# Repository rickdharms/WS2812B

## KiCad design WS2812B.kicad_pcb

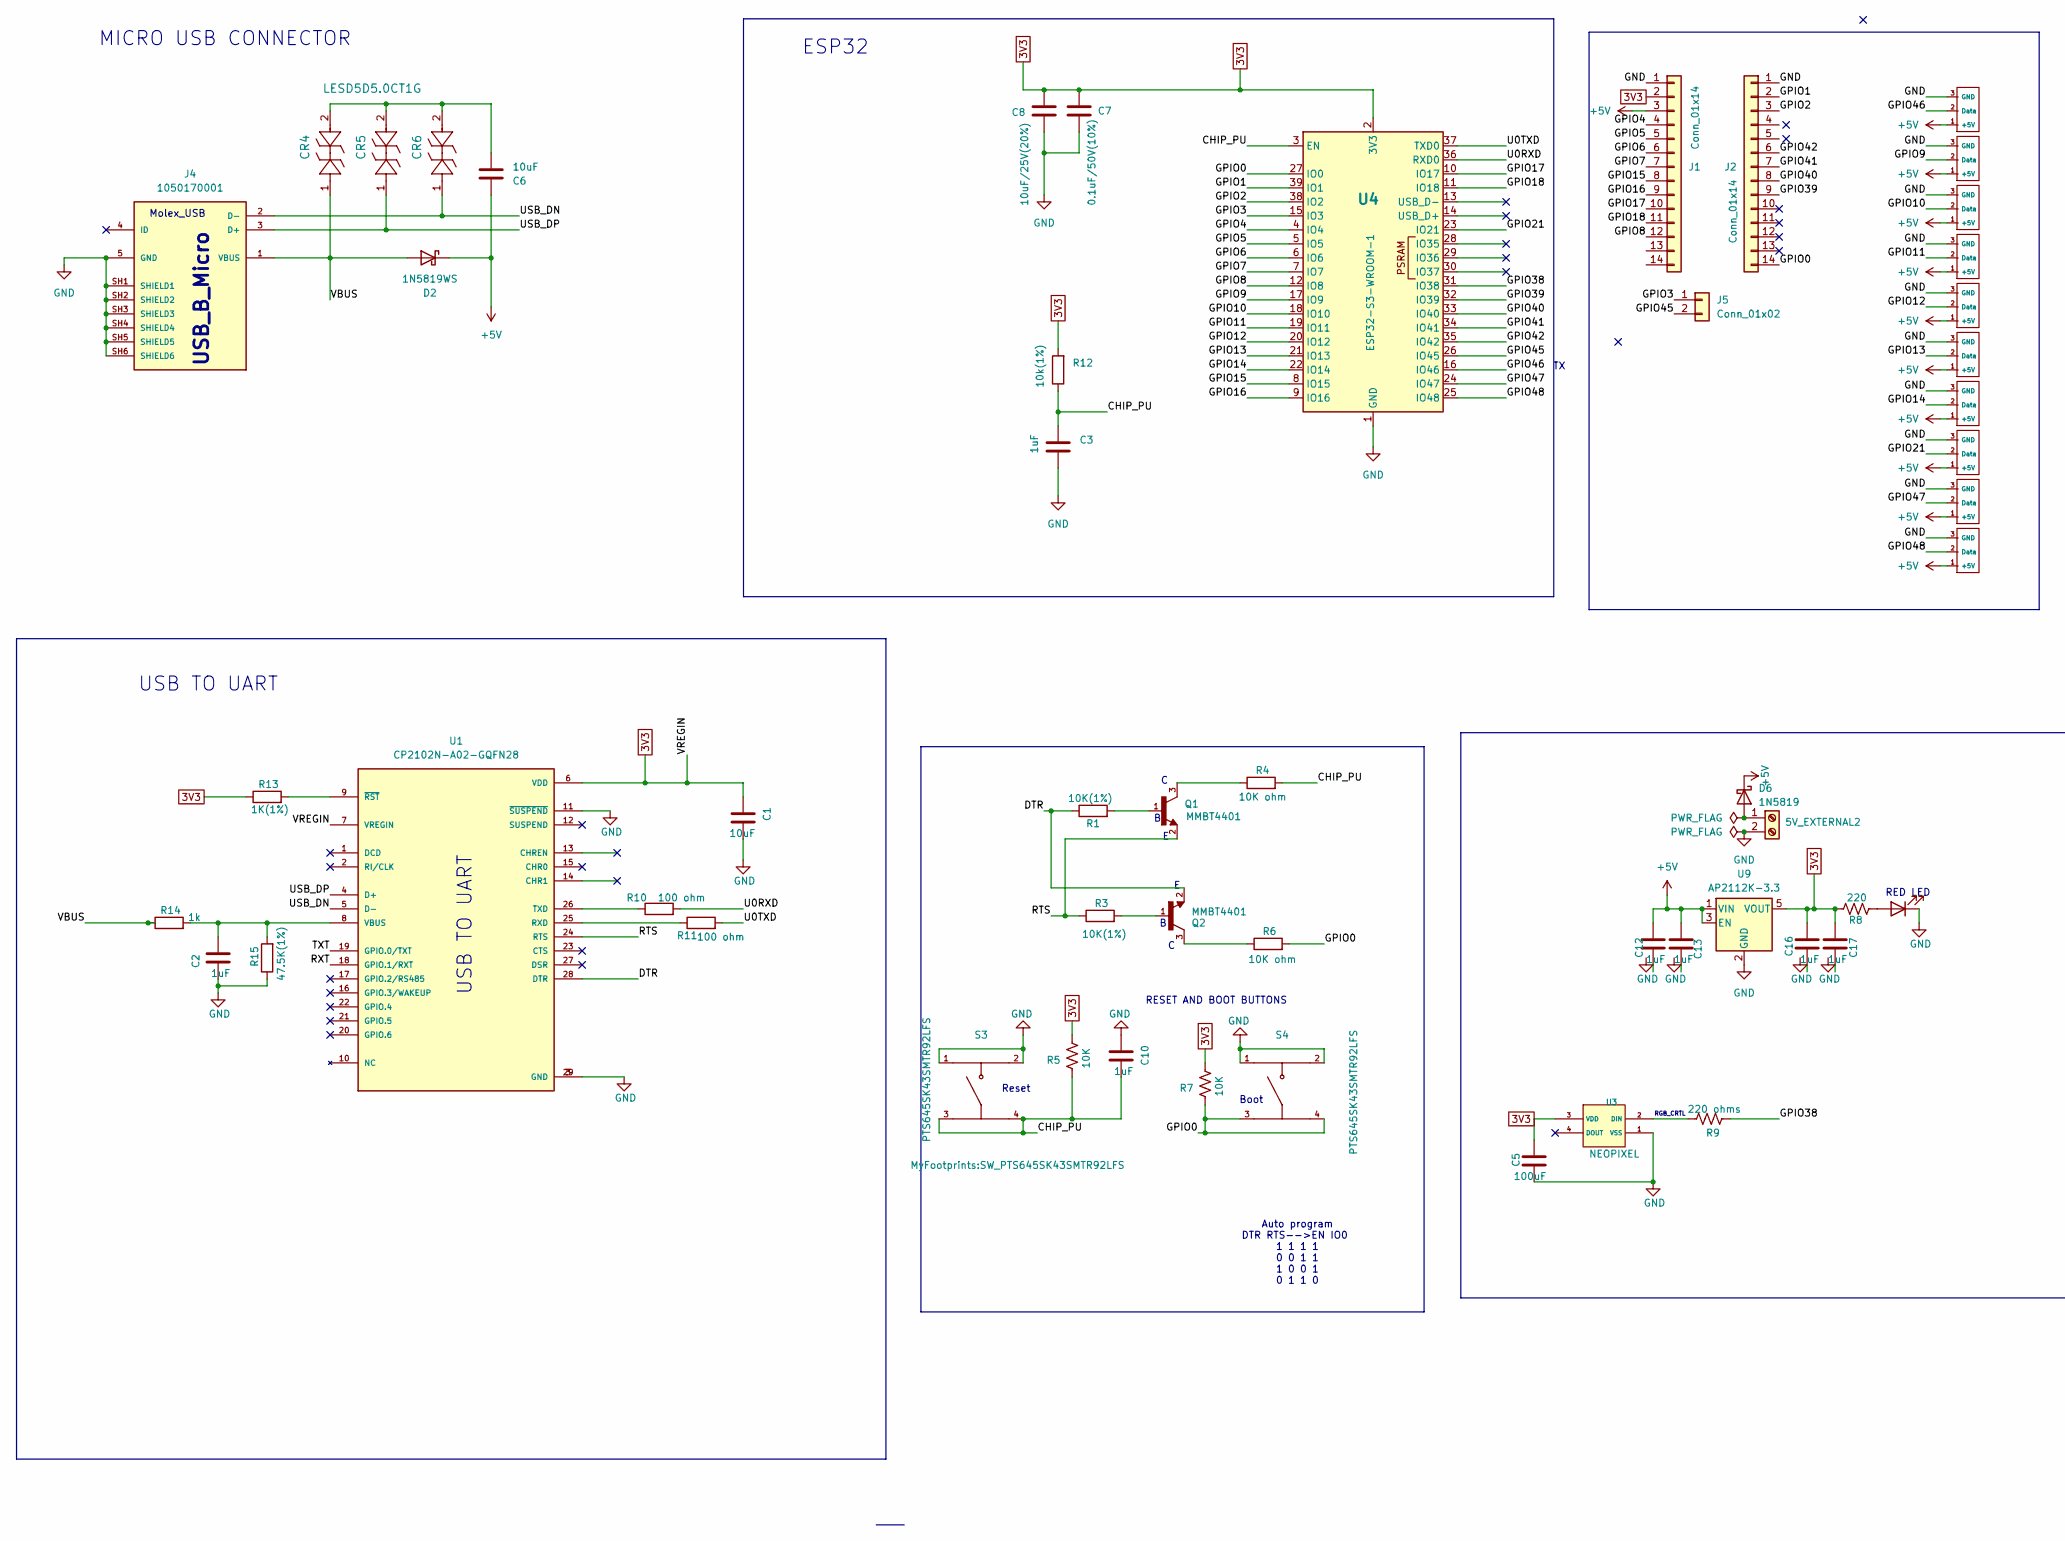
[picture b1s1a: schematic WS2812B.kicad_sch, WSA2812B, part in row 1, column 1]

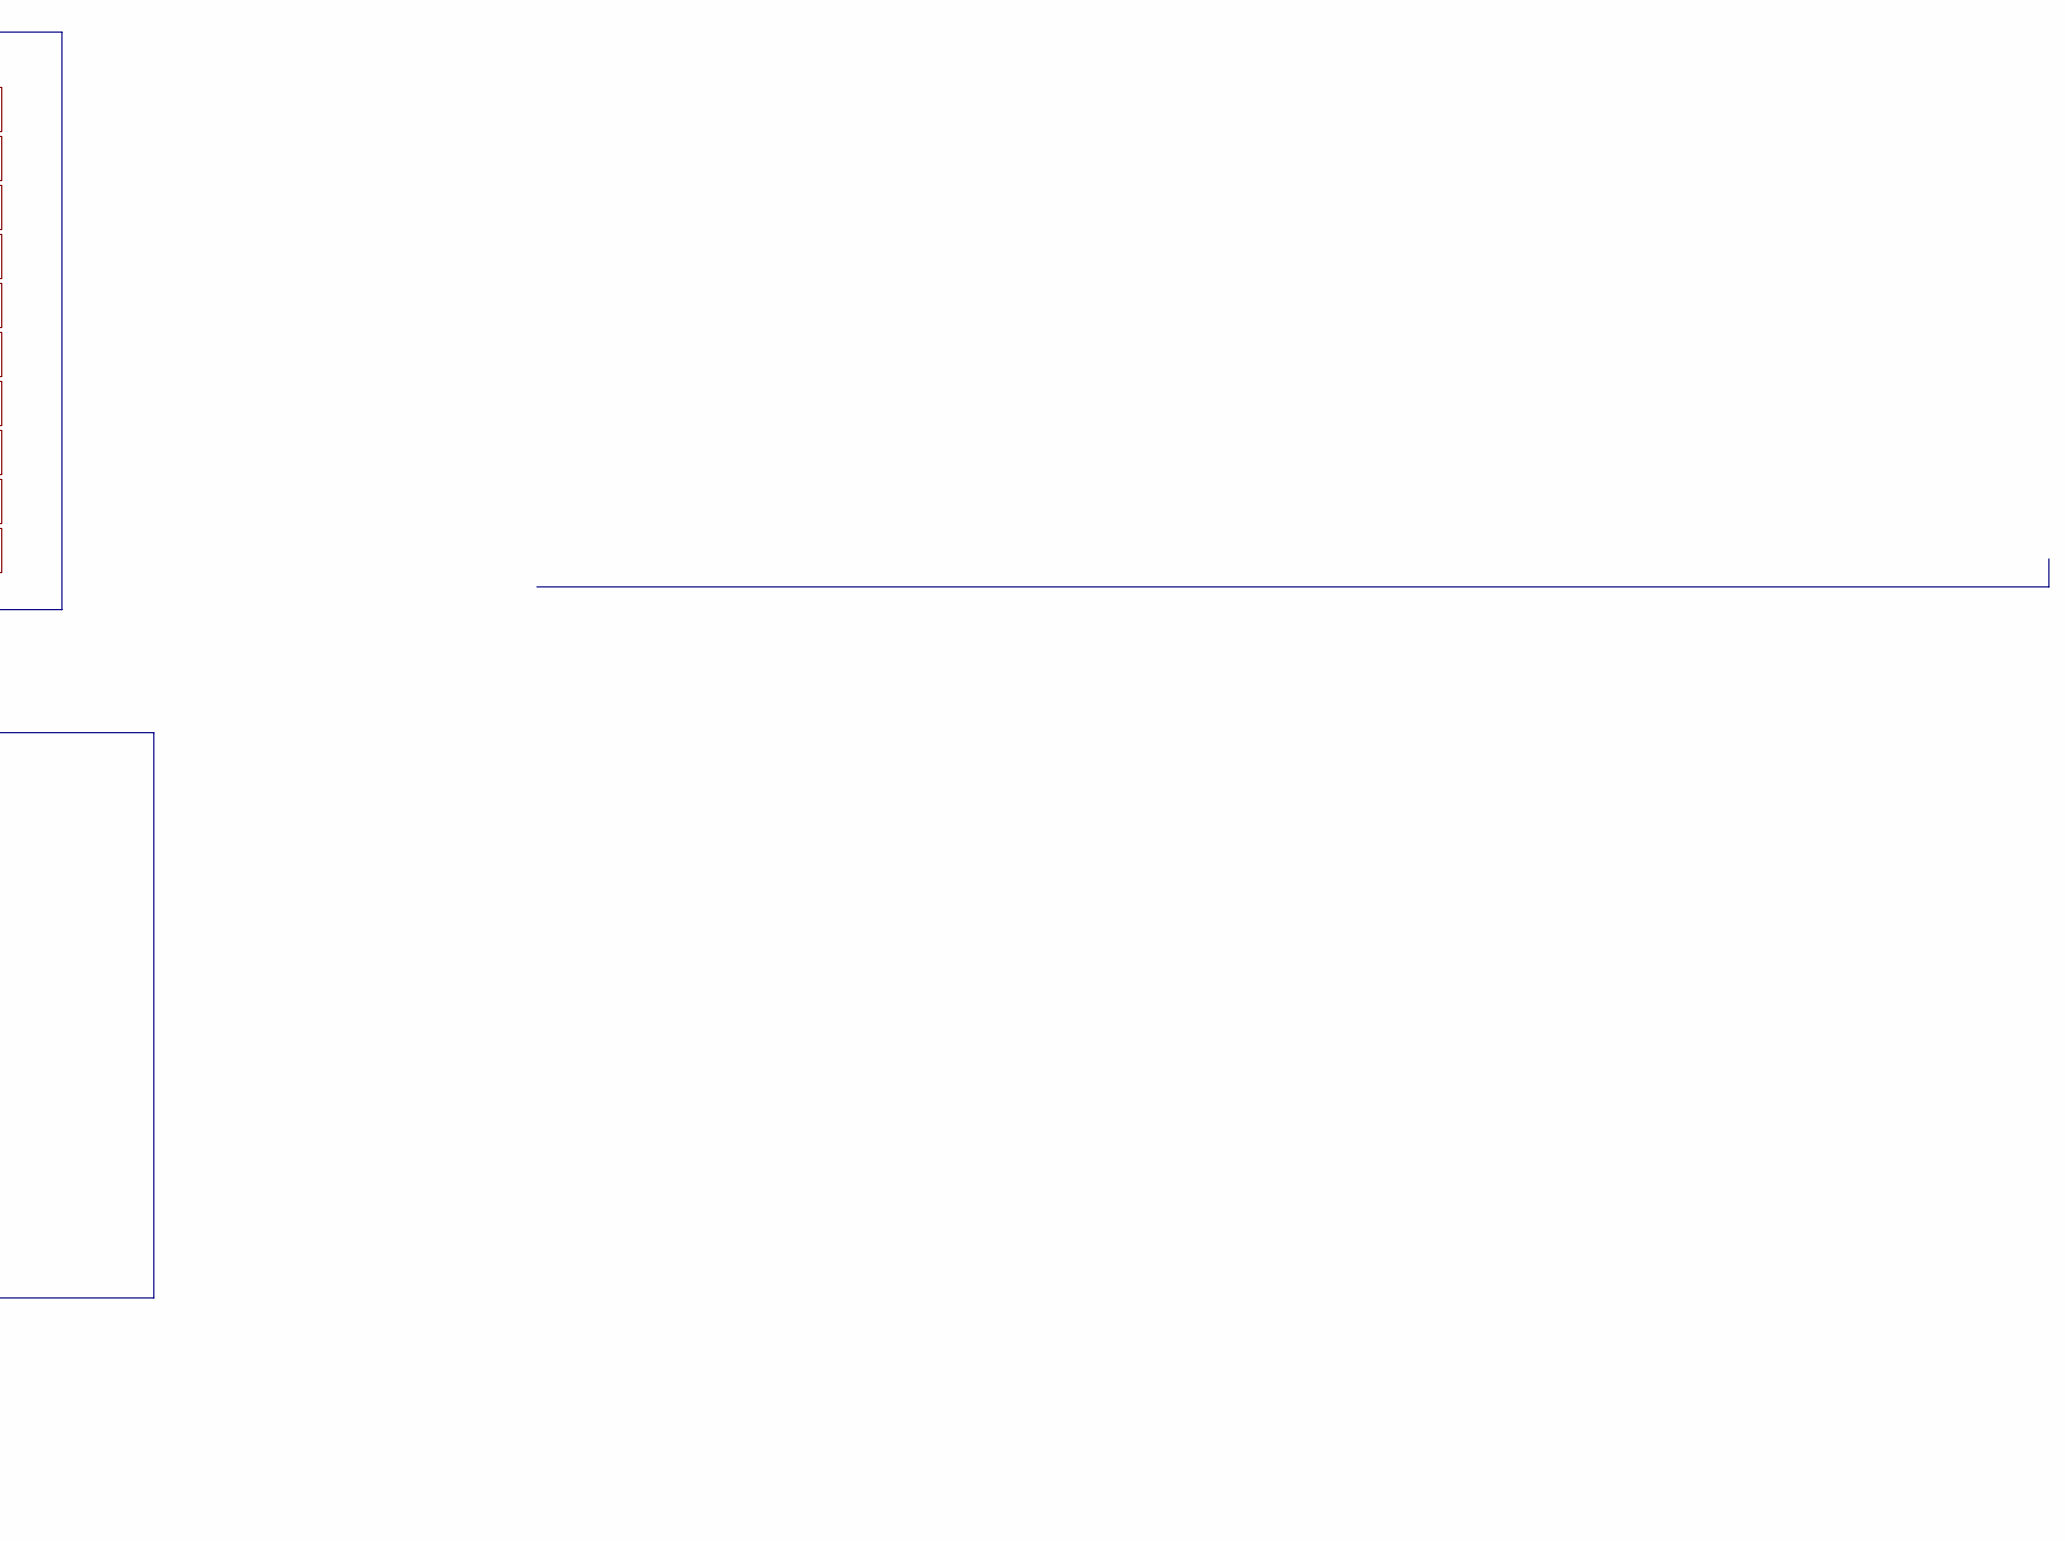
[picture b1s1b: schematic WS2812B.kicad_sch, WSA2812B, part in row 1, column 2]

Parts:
5V_EXTERNAL2: Screw_Terminal_01x02; TerminalBlock_MaiXu_MX126-5.0-02P_1x02_P5.00mm
C1, C6: 10uF; C_0805_2012Metric
C2, C3, C10, C12, C13, C16, C17: 1uF; C_0805_2012Metric
C5: 100uF; C_0805_2012Metric
C7: 0.1uF/50V(10%); C_0805_2012Metric
C8: 10uF/25V(20%); C_0805_2012Metric
CR4, CR5, CR6: LESD5D5.0CT1G; CR_5.0CT1G_UMW
D2: 1N5819WS; D_SOD-323
D6: 1N5819; D_SOD-323_HandSoldering
D7: LED; LED_0805_2012Metric_Pad1.15x1.40mm_HandSolder
J1, J2: Conn_01x14; PinSocket_1x14_P2.54mm_Vertical
J4: 1050170001; MOLEX_1050170001; PARTREV F
J5: Conn_01x02; PinSocket_1x02_P2.54mm_Vertical
Q1, Q2: MMBT4401; TRANS_MMBT4401; DigiKey_Part_Number 4878-MMBT4401TR-ND
R1, R3: 10K(1%); R_0805_2012Metric_Pad1.20x1.40mm_HandSolder
R4, R6: 10K ohm; R_0805_2012Metric_Pad1.20x1.40mm_HandSolder
R5, R7: 10K; R_0805_2012Metric_Pad1.20x1.40mm_HandSolder
R8: 220; R_0805_2012Metric_Pad1.20x1.40mm_HandSolder
R9: 220 ohms; R_0805_2012Metric_Pad1.20x1.40mm_HandSolder
R10, R11: 100 ohm; R_0805_2012Metric_Pad1.20x1.40mm_HandSolder
R12: 10k(1%); R_0805_2012Metric_Pad1.20x1.40mm_HandSolder
R13: 1K(1%); R_0805_2012Metric_Pad1.20x1.40mm_HandSolder
R14: 1k; R_0805_2012Metric_Pad1.20x1.40mm_HandSolder
R15: 47.5K(1%); R_0805_2012Metric_Pad1.20x1.40mm_HandSolder
S3, S4: PTS645SK43SMTR92LFS; SW_PTS645SK43SMTR92LFS; PARTREV 14 Apr 22
U1: CP2102N-A02-GQFN28; QFN50P500X500X80-29N; PARTREV 1.5; DigiKey_Part_Number 336-5889-ND
U2, U5, U6, U7, U8, U10, U11, U12, U13, U14: WS2812B; Three_pad_solder
U3: NEOPIXEL; LED_SK6812MINI_PLCC4_3.5x3.5mm_P1.75mm
U4: ESP32-S3-WROOM-1
U9: AP2112K-3.3; SOT-23-5

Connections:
3V3: C1.2, C5.2, C7.1, C8.2, C16.2, C17.2, J1.2, R5.2, R7.2, R8.1, R12.2, R13.1, U1.6 (VDD), U1.7 (VREGIN), U3.3 (VDD), U4.2 (3V3), U9.5 (VOUT)
+5V: C6.1, C12.2, C13.2, D2.1 (K), D6.1 (K), J1.3, U2.1 (+5V), U5.1 (+5V), U6.1 (+5V), U7.1 (+5V), U8.1 (+5V), U9.1 (VIN), U9.3 (EN), U10.1 (+5V), U11.1 (+5V), U12.1 (+5V), U13.1 (+5V), U14.1 (+5V)
/CHIP_PU: C3.1, C10.1, R4.2, R5.1, R12.1, S3.3, S3.4, U4.3 (EN)
/DTR: Q2.2, R1.1, U1.28 (DTR)
/GPIO0: J2.14, R6.2, R7.1, S4.3, S4.4, U4.27 (IO0)
/GPIO1: J2.2, U4.39 (IO1)
/GPIO2: J2.3, U4.38 (IO2)
/GPIO3: J5.1, U4.15 (IO3)
/GPIO4: J1.4, U4.4 (IO4)
/GPIO5: J1.5, U4.5 (IO5)
/GPIO6: J1.6, U4.6 (IO6)
/GPIO7: J1.7, U4.7 (IO7)
/GPIO8: J1.12, U4.12 (IO8)
/GPIO9: U4.17 (IO9), U5.2 (Data)
/GPIO10: U4.18 (IO10), U6.2 (Data)
/GPIO11: U4.19 (IO11), U7.2 (Data)
/GPIO12: U4.20 (IO12), U8.2 (Data)
/GPIO13: U4.21 (IO13), U10.2 (Data)
/GPIO14: U4.22 (IO14), U11.2 (Data)
/GPIO15: J1.8, U4.8 (IO15)
/GPIO16: J1.9, U4.9 (IO16)
/GPIO17: J1.10, U4.10 (IO17)
/GPIO18: J1.11, U4.11 (IO18)
/GPIO21: U4.23 (IO21), U12.2 (Data)
/GPIO38: R9.2, U4.31 (IO38)
/GPIO39: J2.9, U4.32 (IO39)
/GPIO40: J2.8, U4.33 (IO40)
/GPIO41: J2.7, U4.34 (IO41)
/GPIO42: J2.6, U4.35 (IO42)
/GPIO45: J5.2, U4.26 (IO45)
/GPIO46: U2.2 (Data), U4.16 (IO46)
/GPIO47: U4.24 (IO47), U13.2 (Data)
/GPIO48: U4.25 (IO48), U14.2 (Data)
/RTS: Q1.2, R3.1, U1.24 (RTS)
/RXT: U1.18 (GPIO.1/RXT)
/TXT: U1.19 (GPIO.0/TXT)
/U0RXD: R10.2, U4.36 (RXD0)
/U0TXD: R11.2, U4.37 (TXD0)
/USB_DN: CR6.1, J4.2 (D-), U1.5 (D-)
/USB_DP: CR5.1, J4.3 (D+), U1.4 (D+)
/VBUS: CR4.1, D2.2 (A), J4.1 (VBUS), R14.1
GND: 5V_EXTERNAL2.2, C1.1, C2.1, C3.2, C5.1, C7.2, C8.1, C10.2, D7.1 (K), J1.1, J2.1, J4.5 (GND), J4.SH1 (SHIELD1), J4.SH2 (SHIELD2), J4.SH3 (SHIELD3), J4.SH4 (SHIELD4), J4.SH5 (SHIELD5), J4.SH6 (SHIELD6), R15.1, S3.1, S3.2, S4.1, S4.2, U1.3 (GND), U1.11 (~SUSPEND), U1.29 (GND), U2.3 (GND), U3.1 (VSS), U4.1 (GND), U4.40 (GND), U4.41 (GND), U5.3 (GND), U6.3 (GND), U7.3 (GND), U8.3 (GND), U9.2 (GND), U10.3 (GND), U11.3 (GND), U12.3 (GND), U13.3 (GND), U14.3 (GND)
unnamed: 5V_EXTERNAL2.1, D6.2 (A)
unnamed: C6.2, CR4.2, CR5.2, CR6.2
unnamed: D7.2 (A), R8.2
unnamed: Q1.1, R1.2
unnamed: Q1.3, R4.1
unnamed: Q2.1, R3.2
unnamed: Q2.3, R6.1
unnamed: R11.1, U1.25 (RXD)
unnamed: R10.1, U1.26 (TXD)
unnamed: C2.2, R14.2, R15.2, U1.8 (VBUS)
unnamed: R13.2, U1.9 (~RST)
unnamed: R9.1, U3.2 (DIN)

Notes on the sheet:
ESP32
Reset
USB TO UART
Auto program DTR RTS-->EN IO0 1 1 1 1 0 0 1 1 1 0 0 1 0 1 1 0
USB_B_Micro
RGB_CRTL
RED LED
Boot
RESET AND BOOT BUTTONS
Molex_USB
MICRO USB CONNECTOR

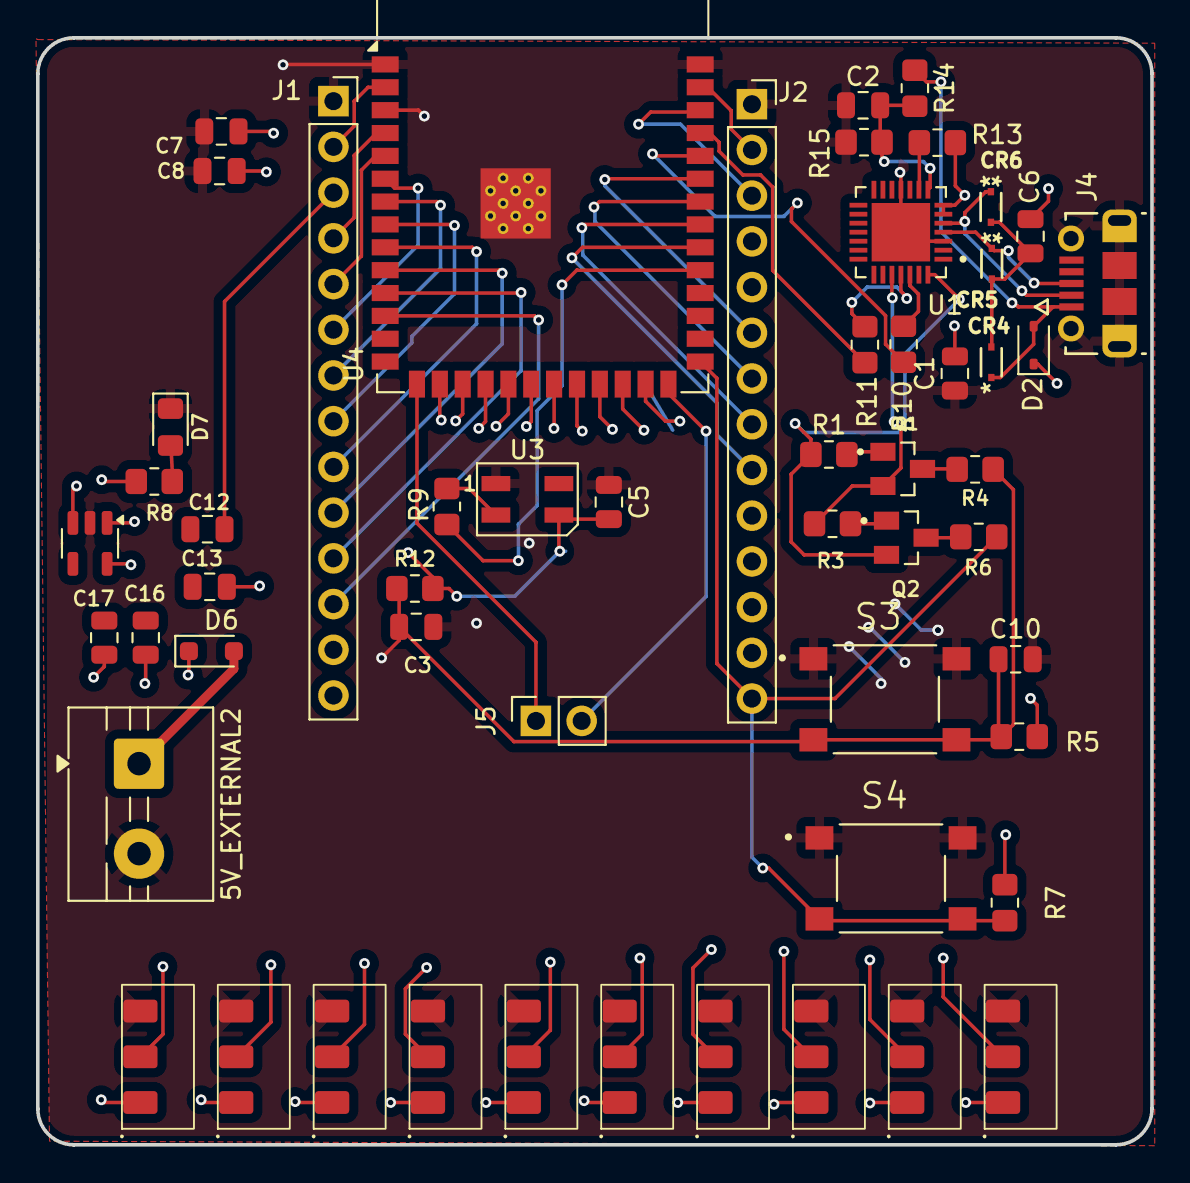
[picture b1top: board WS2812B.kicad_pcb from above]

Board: 4 copper layers, 61.9 x 61.5 mm, 55 parts (0 on the bottom side), 52 nets.

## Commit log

2025-08-08 ESP32_WS2812B driver
